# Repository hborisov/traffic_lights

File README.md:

# traffic_lights
These are various files related to the traffic lights project located at http://hristoborisov.com/index.php/projects/usb-hid-traffic-lights-device-with-pic18/

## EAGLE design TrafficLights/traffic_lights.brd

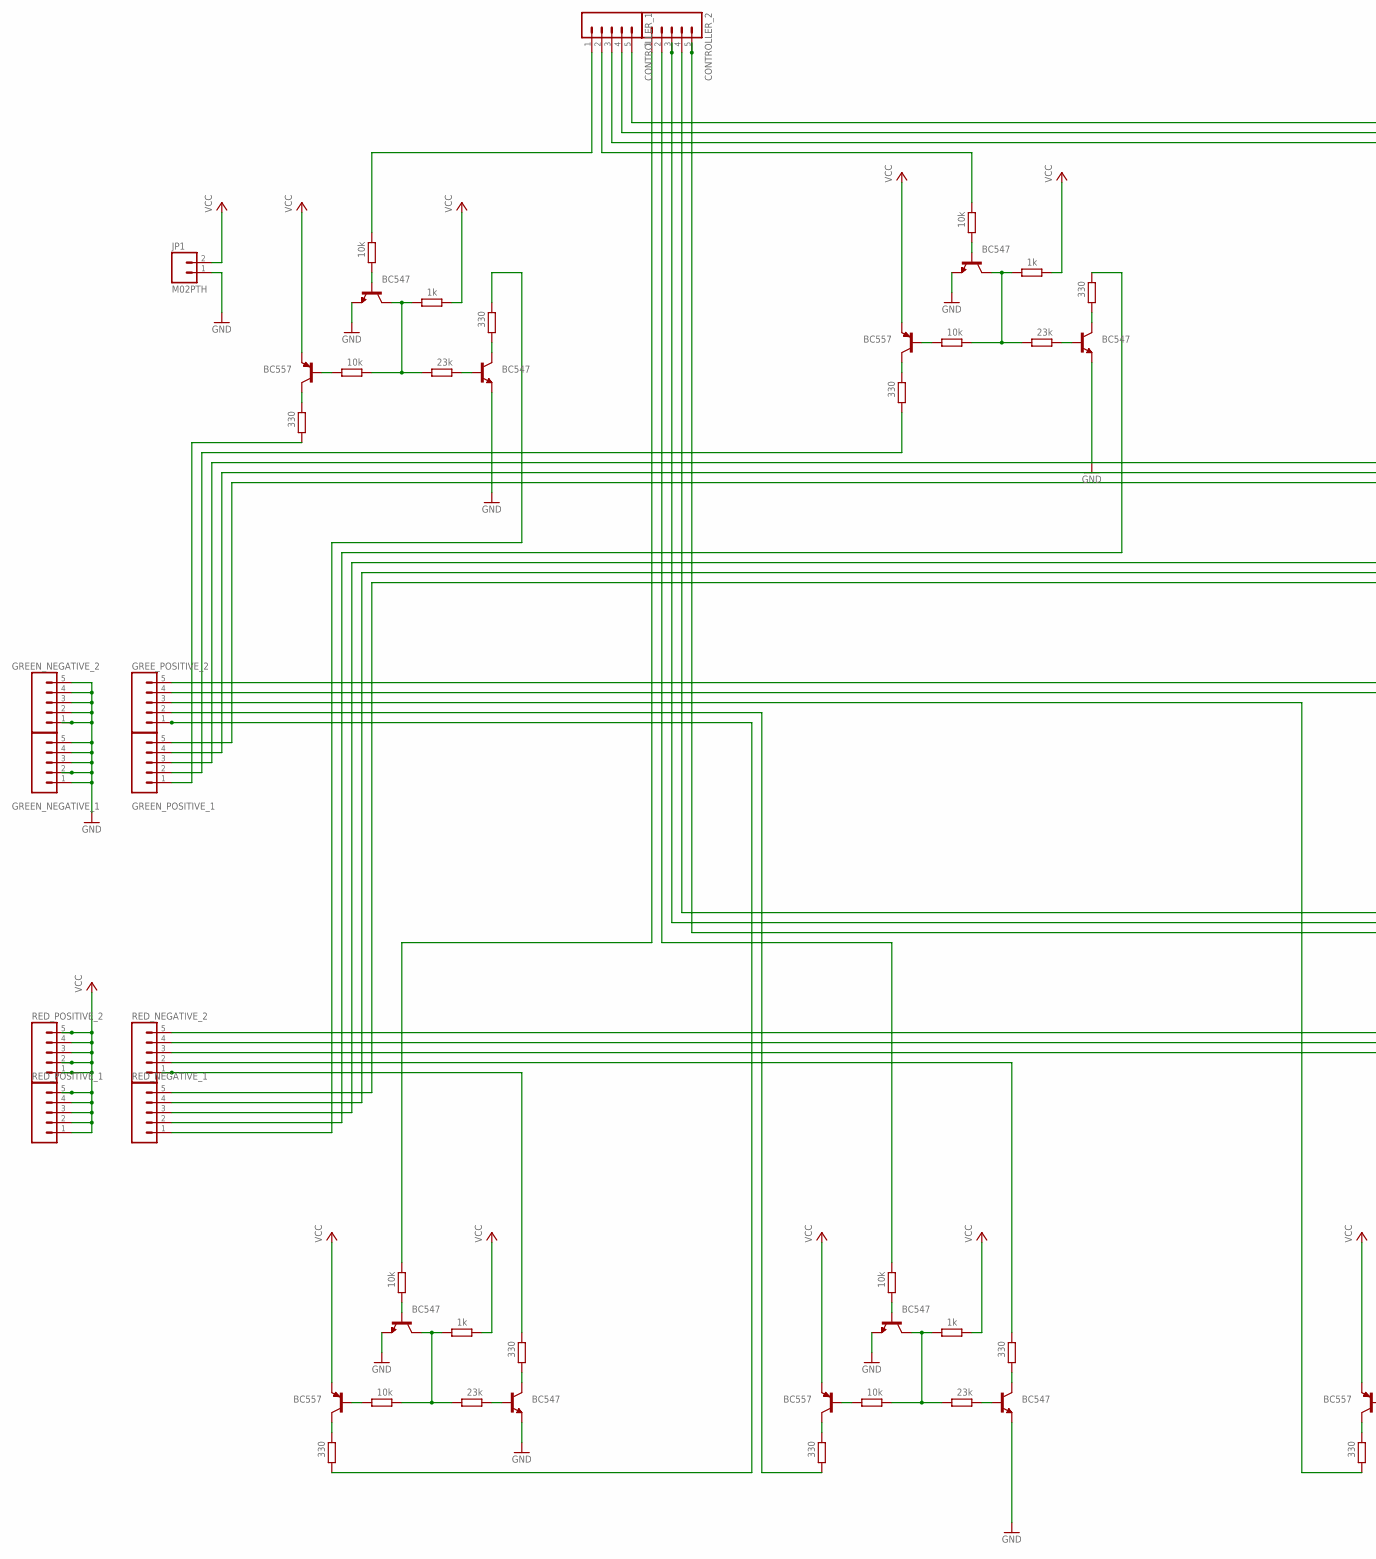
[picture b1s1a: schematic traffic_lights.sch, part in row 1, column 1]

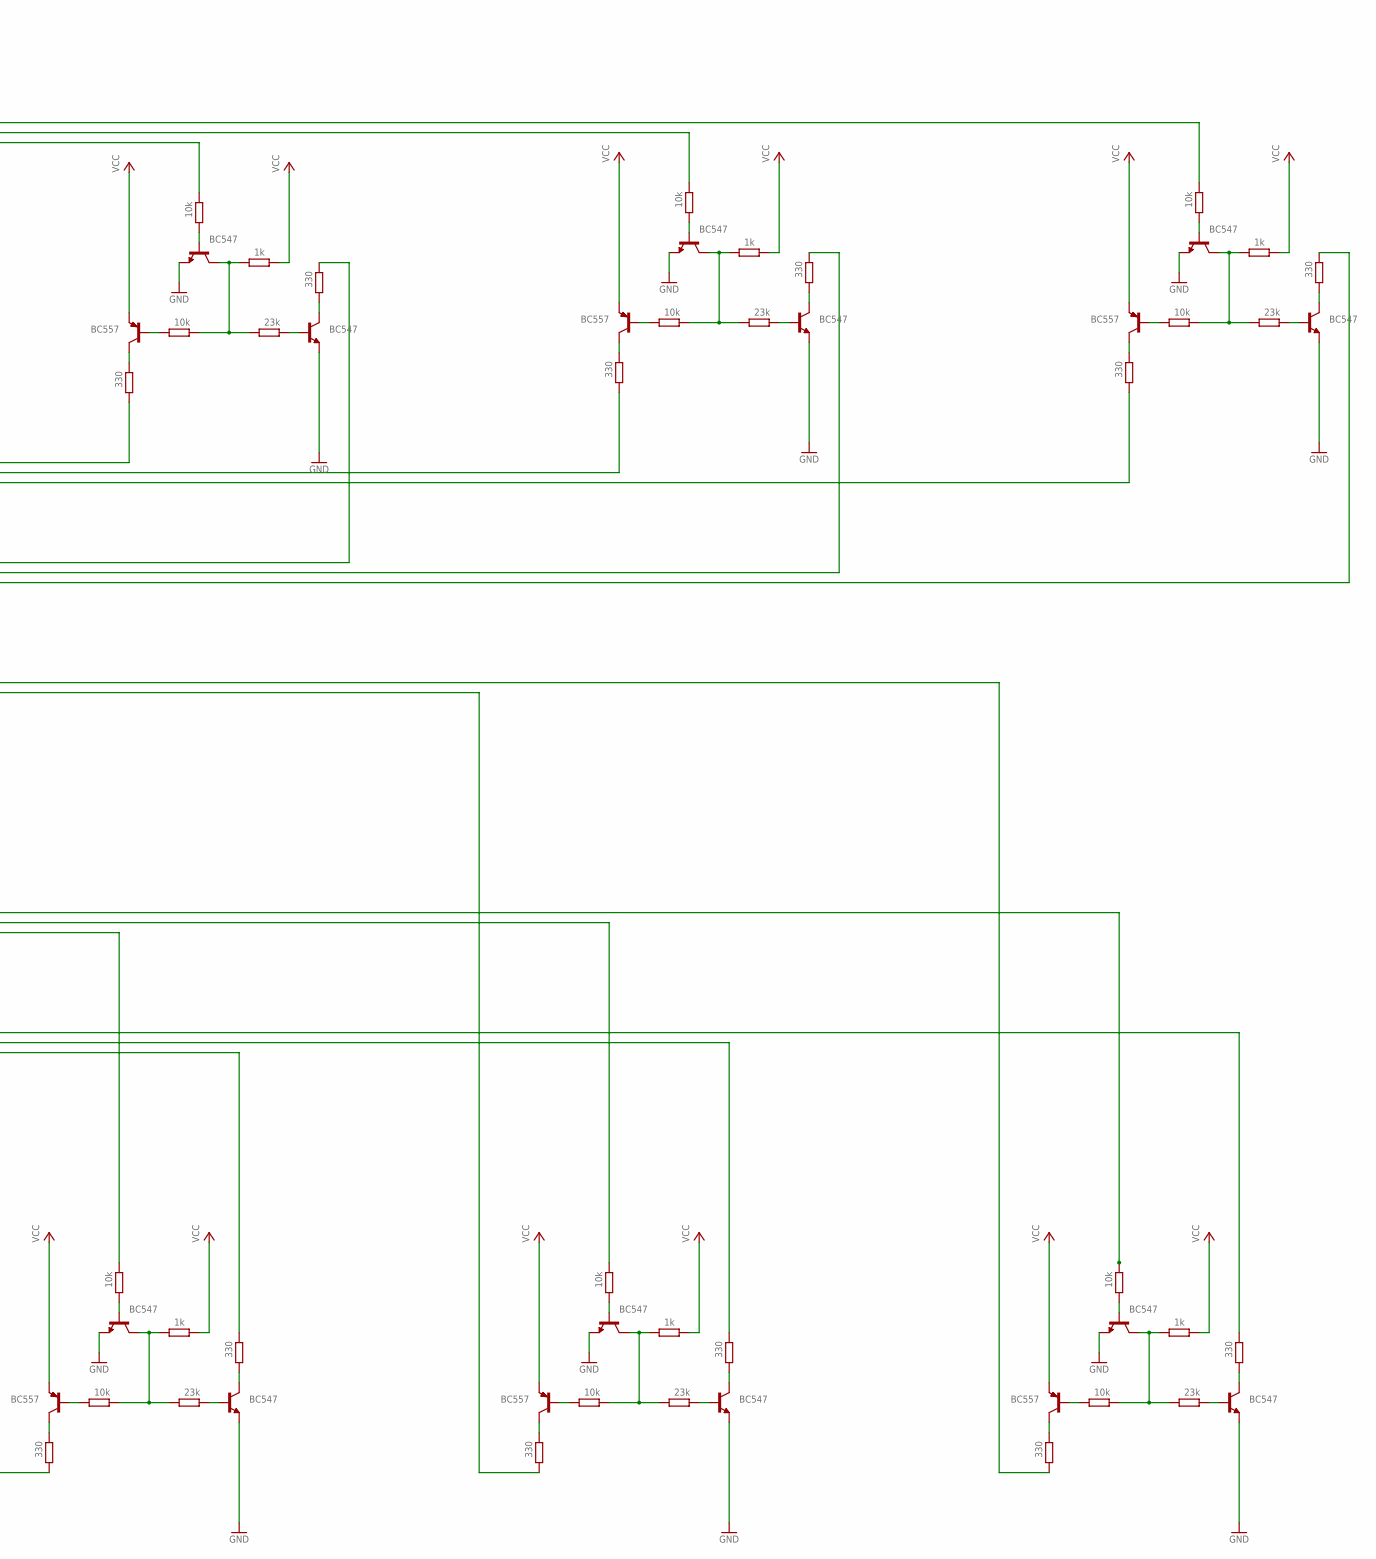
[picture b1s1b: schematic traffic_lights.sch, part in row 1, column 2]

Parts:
CONTROLLER_1, CONTROLLER_2: M05PTH; 1X05
GREEN_NEGATIVE_1, GREEN_NEGATIVE_2: M05PTH; 1X05
GREEN_POSITIVE_1: M05PTH; 1X05
GREE_POSITIVE_2: M05PTH; 1X05
JP1: M02PTH; 1X02
RC1, RC4, RC21, RC24, RC31, RC34, RC41, RC44, RC51, RC54, RC61, RC64, RC71, RC74, RC81, RC84, RC91, RC94, RC101, RC104: 10k; 0207/10
RC2, RC22, RC32, RC42, RC52, RC62, RC72, RC82, RC92, RC102: 1k; 0207/10
RC3, RC23, RC33, RC43, RC53, RC63, RC73, RC83, RC93, RC103: 23k; 0207/10
RC5, RC6, RC25, RC26, RC35, RC36, RC45, RC46, RC55, RC56, RC65, RC66, RC75, RC76, RC85, RC86, RC95, RC96, RC105, RC106: 330; 0207/10
RED_NEGATIVE_1, RED_NEGATIVE_2: M05PTH; 1X05
RED_POSITIVE_1, RED_POSITIVE_2: M05PTH; 1X05
TCTRL1, TCTRL2, TCTRL3, TCTRL4, TCTRL5, TCTRL6, TCTRL7, TCTRL8, TCTRL9, TCTRL10: BC547; TO92
TGR1, TGR2, TGR3, TGR4, TGR5, TGR6, TGR7, TGR8, TGR9, TGR10: BC547; TO92
TR1, TR2, TR3, TR4, TR5, TR6, TR7, TR8, TR9, TR10: BC557; TO92

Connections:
GND: GREEN_NEGATIVE_1.1, GREEN_NEGATIVE_1.2, GREEN_NEGATIVE_1.3, GREEN_NEGATIVE_1.4, GREEN_NEGATIVE_1.5, GREEN_NEGATIVE_2.1, GREEN_NEGATIVE_2.2, GREEN_NEGATIVE_2.3, GREEN_NEGATIVE_2.4, GREEN_NEGATIVE_2.5, JP1.1, TCTRL1.1 (E), TCTRL2.1 (E), TCTRL3.1 (E), TCTRL4.1 (E), TCTRL5.1 (E), TCTRL6.1 (E), TCTRL7.1 (E), TCTRL8.1 (E), TCTRL9.1 (E), TCTRL10.1 (E), TGR1.1 (E), TGR2.1 (E), TGR3.1 (E), TGR4.1 (E), TGR5.1 (E), TGR6.1 (E), TGR7.1 (E), TGR8.1 (E), TGR9.1 (E), TGR10.1 (E)
unnamed: GREEN_POSITIVE_1.1, RC6.1
unnamed: RC21.1, TCTRL2.2 (B)
unnamed: RC24.1, TR2.2 (B)
unnamed: RC2.1, RC3.1, RC4.2, TCTRL1.3 (C)
unnamed: RC1.1, TCTRL1.2 (B)
unnamed: RC4.1, TR1.2 (B)
unnamed: RC6.2, TR1.3 (C)
unnamed: RC26.2, TR2.3 (C)
unnamed: RC35.2, RED_NEGATIVE_1.3
unnamed: RC5.1, TGR1.3 (C)
unnamed: RC3.2, TGR1.2 (B)
unnamed: CONTROLLER_1.1, RC1.2
unnamed: RC25.2, RED_NEGATIVE_1.2
unnamed: RC25.1, TGR2.3 (C)
unnamed: RC23.2, TGR2.2 (B)
unnamed: CONTROLLER_1.2, RC21.2
unnamed: RC22.1, RC23.1, RC24.2, TCTRL2.3 (C)
unnamed: CONTROLLER_1.3, RC31.2
unnamed: RC31.1, TCTRL3.2 (B)
unnamed: RC34.1, TR3.2 (B)
unnamed: RC36.2, TR3.3 (C)
unnamed: RC45.2, RED_NEGATIVE_1.4
unnamed: RC35.1, TGR3.3 (C)
unnamed: RC33.2, TGR3.2 (B)
unnamed: CONTROLLER_1.4, RC41.2
unnamed: RC32.1, RC33.1, RC34.2, TCTRL3.3 (C)
unnamed: GREEN_POSITIVE_1.2, RC26.1
unnamed: RC41.1, TCTRL4.2 (B)
unnamed: RC44.1, TR4.2 (B)
unnamed: RC46.2, TR4.3 (C)
unnamed: RC55.2, RED_NEGATIVE_1.5
unnamed: RC45.1, TGR4.3 (C)
unnamed: RC43.2, TGR4.2 (B)
unnamed: CONTROLLER_1.5, RC51.2
unnamed: RC42.1, RC43.1, RC44.2, TCTRL4.3 (C)
unnamed: GREEN_POSITIVE_1.4, RC46.1
unnamed: RC51.1, TCTRL5.2 (B)
unnamed: RC54.1, TR5.2 (B)
unnamed: RC56.2, TR5.3 (C)
unnamed: GREEN_POSITIVE_1.3, RC36.1
unnamed: RC55.1, TGR5.3 (C)
unnamed: RC53.2, TGR5.2 (B)
unnamed: RC5.2, RED_NEGATIVE_1.1
unnamed: RC52.1, RC53.1, RC54.2, TCTRL5.3 (C)
unnamed: GREEN_POSITIVE_1.5, RC56.1
unnamed: RC71.1, TCTRL7.2 (B)
unnamed: RC74.1, TR7.2 (B)
unnamed: RC76.2, TR7.3 (C)
unnamed: RC75.2, RED_NEGATIVE_2.2
unnamed: RC75.1, TGR7.3 (C)
unnamed: RC73.2, TGR7.2 (B)
unnamed: CONTROLLER_2.1, RC61.2
unnamed: RC72.1, RC73.1, RC74.2, TCTRL7.3 (C)
unnamed: RC85.2, RED_NEGATIVE_2.3
unnamed: RC81.1, TCTRL8.2 (B)
unnamed: RC84.1, TR8.2 (B)
unnamed: RC86.2, TR8.3 (C)
unnamed: RC95.2, RED_NEGATIVE_2.4
unnamed: RC85.1, TGR8.3 (C)
unnamed: RC83.2, TGR8.2 (B)
unnamed: CONTROLLER_2.2, RC71.2
unnamed: RC82.1, RC83.1, RC84.2, TCTRL8.3 (C)
unnamed: RC105.2, RED_NEGATIVE_2.5
unnamed: RC91.1, TCTRL9.2 (B)
unnamed: RC94.1, TR9.2 (B)
unnamed: RC96.2, TR9.3 (C)
unnamed: GREE_POSITIVE_2.1, RC66.1
unnamed: RC95.1, TGR9.3 (C)
unnamed: RC93.2, TGR9.2 (B)
unnamed: CONTROLLER_2.5, RC81.2
unnamed: RC92.1, RC93.1, RC94.2, TCTRL9.3 (C)
unnamed: GREE_POSITIVE_2.2, RC76.1
unnamed: RC101.1, TCTRL10.2 (B)
unnamed: RC104.1, TR10.2 (B)
unnamed: RC106.2, TR10.3 (C)
unnamed: GREE_POSITIVE_2.3, RC86.1
unnamed: RC105.1, TGR10.3 (C)
unnamed: RC103.2, TGR10.2 (B)
unnamed: CONTROLLER_2.3, RC91.2
unnamed: RC102.1, RC103.1, RC104.2, TCTRL10.3 (C)
unnamed: GREE_POSITIVE_2.4, RC96.1
unnamed: RC61.1, TCTRL6.2 (B)
unnamed: RC64.1, TR6.2 (B)
unnamed: RC66.2, TR6.3 (C)
unnamed: RC65.2, RED_NEGATIVE_2.1
unnamed: RC65.1, TGR6.3 (C)
unnamed: RC63.2, TGR6.2 (B)
unnamed: GREE_POSITIVE_2.5, RC106.1
unnamed: RC62.1, RC63.1, RC64.2, TCTRL6.3 (C)
unnamed: CONTROLLER_2.4, RC101.2
VCC: JP1.2, RC2.2, RC22.2, RC32.2, RC42.2, RC52.2, RC62.2, RC72.2, RC82.2, RC92.2, RC102.2, RED_POSITIVE_1.1, RED_POSITIVE_1.2, RED_POSITIVE_1.3, RED_POSITIVE_1.4, RED_POSITIVE_1.5, RED_POSITIVE_2.1, RED_POSITIVE_2.2, RED_POSITIVE_2.3, RED_POSITIVE_2.4, RED_POSITIVE_2.5, TR1.1 (E), TR2.1 (E), TR3.1 (E), TR4.1 (E), TR5.1 (E), TR6.1 (E), TR7.1 (E), TR8.1 (E), TR9.1 (E), TR10.1 (E)

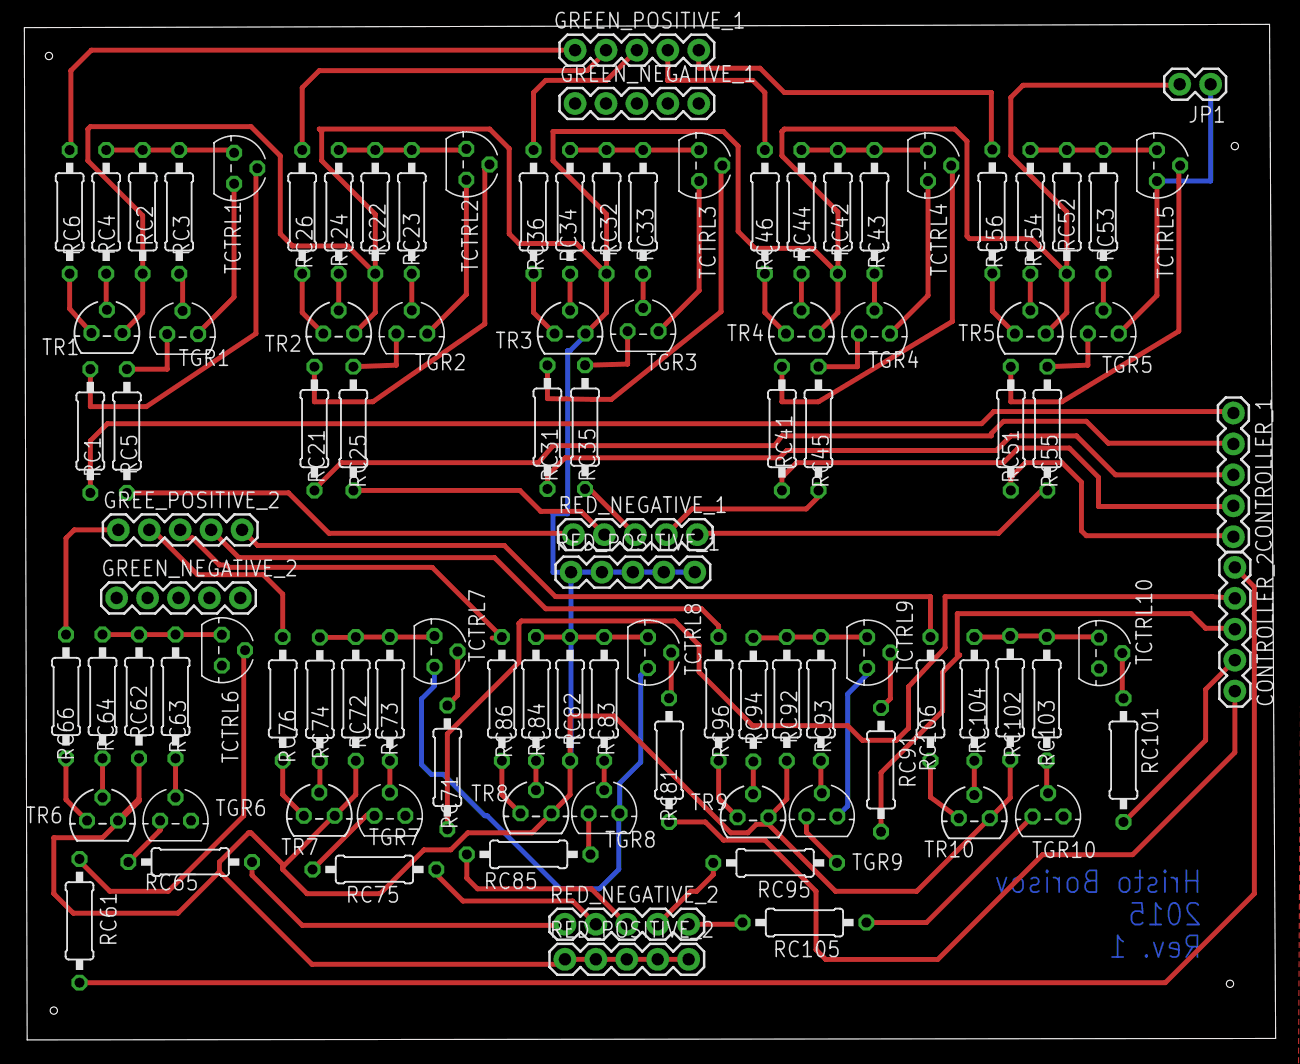
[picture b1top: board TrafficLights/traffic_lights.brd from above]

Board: 2 copper layers, 102.8 x 83.4 mm, 101 parts (0 on the bottom side), 92 nets.

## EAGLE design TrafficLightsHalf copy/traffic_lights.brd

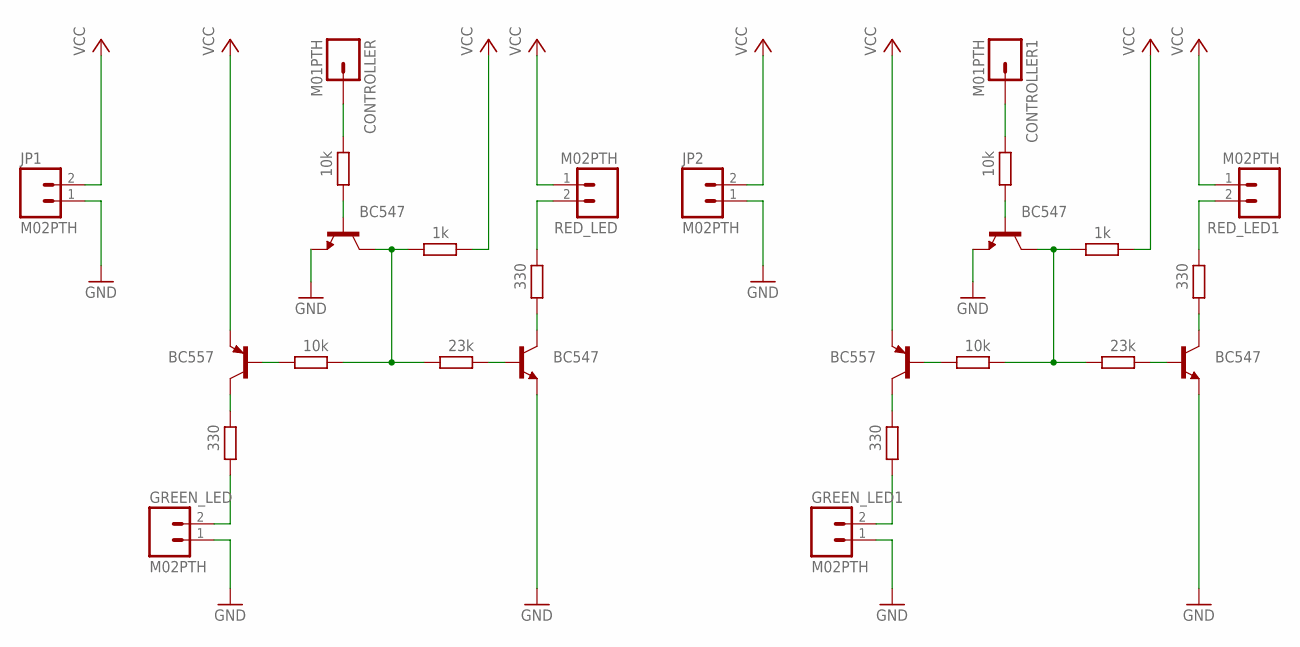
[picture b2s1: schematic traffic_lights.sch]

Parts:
CONTROLLER, CONTROLLER1: M01PTH; 1X01
GREEN_LED, GREEN_LED1: M02PTH; 1X02
JP1, JP2: M02PTH; 1X02
Q1, Q2: BC557; TO92
R1, R2, R5, R8: 10k; 0207/10
R3, R4: 23k; 0207/10
R6, R9: 1k; 0207/10
R7, R10, R11, R12: 330; 0207/10
RED_LED, RED_LED1: M02PTH; 1X02
T1, T2, T3, T4: BC547; TO92

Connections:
GND: GREEN_LED.1, GREEN_LED1.1, JP1.1, JP2.1, T1.1 (E), T2.1 (E), T3.1 (E), T4.1 (E)
unnamed: CONTROLLER.1, R8.2
unnamed: R10.2, RED_LED.2
unnamed: GREEN_LED.2, R11.1
unnamed: R2.2, R3.1, R9.1, T2.3 (C)
unnamed: R8.1, T2.2 (B)
unnamed: Q1.2 (B), R2.1
unnamed: Q1.3 (C), R11.2
unnamed: R5.1, T4.2 (B)
unnamed: Q2.2 (B), R1.1
unnamed: R10.1, T1.3 (C)
unnamed: R3.2, T1.2 (B)
unnamed: Q2.3 (C), R12.2
unnamed: R7.1, T3.3 (C)
unnamed: R4.2, T3.2 (B)
unnamed: R1.2, R4.1, R6.1, T4.3 (C)
unnamed: R7.2, RED_LED1.2
unnamed: GREEN_LED1.2, R12.1
unnamed: CONTROLLER1.1, R5.2
VCC: JP1.2, JP2.2, Q1.1 (E), Q2.1 (E), R6.2, R9.2, RED_LED.1, RED_LED1.1

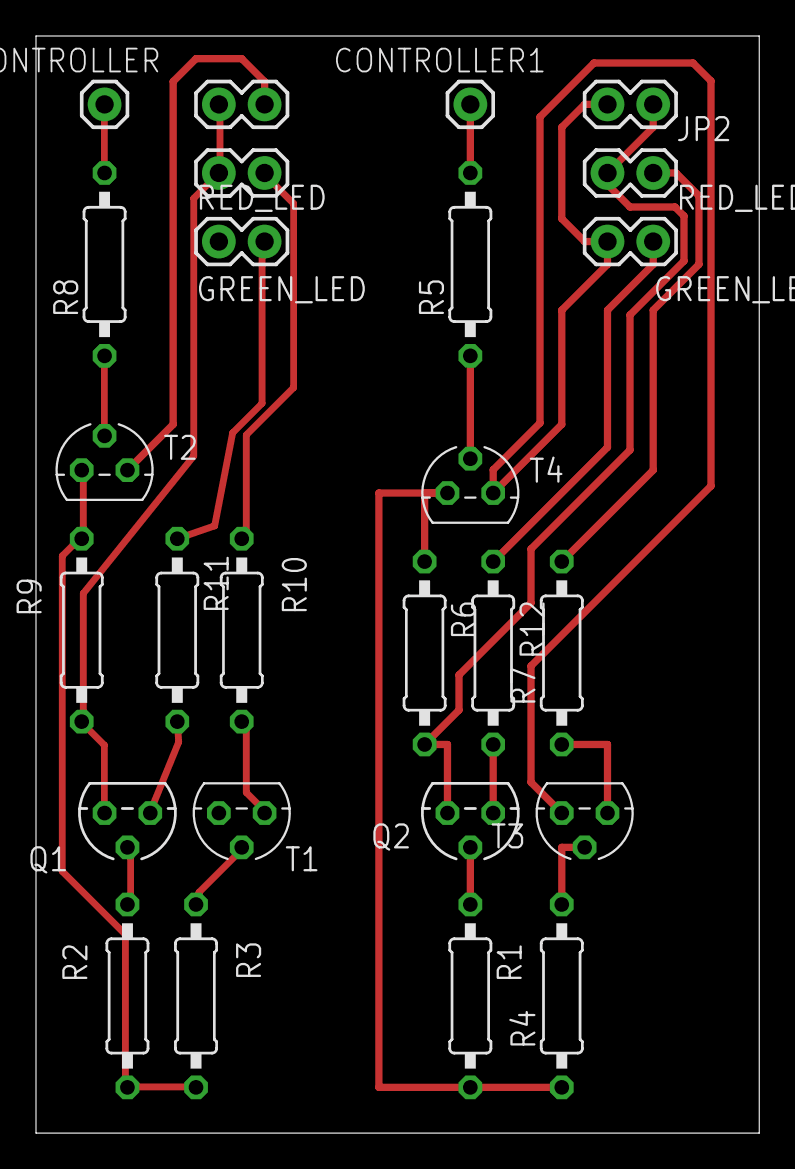
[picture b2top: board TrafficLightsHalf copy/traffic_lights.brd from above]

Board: 2 copper layers, 40.2 x 61.0 mm, 26 parts (0 on the bottom side), 20 nets.

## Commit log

2015-10-24 Adding the Eagle projects together with schematics for laser cutting a box for the device

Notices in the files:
parts and their libraries:
SparkFun-Connectors: Licensing: Creative Commons ShareAlike 4.0 International - https://creativecommons.org/licenses/by-sa/4.0
